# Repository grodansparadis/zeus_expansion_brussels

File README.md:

<h1>Zeus Expansion Brussels</h1>

Temperature add on card with Zeus expansion connector. Fits the 
<a href="http://www.grodansparadis.com/odessa/odessa.html">Odessa</a> module
among other modules.

<hr>

This project is part of the <a href="http://www.vscp.org">VSCP (Very Simple Control Protocol) project</a>. 

<hr>

This project is licensed under the 
<a href="http://creativecommons.org/licenses/by-nc-sa/3.0/">Creative Commons open source license Attribution-NonCommercial-ShareAlike 3.0 Unported</a>. 
Other license options are available by conacting <a href="malto:info@grodansparadis.com">Paradis of the Frog AB</a>

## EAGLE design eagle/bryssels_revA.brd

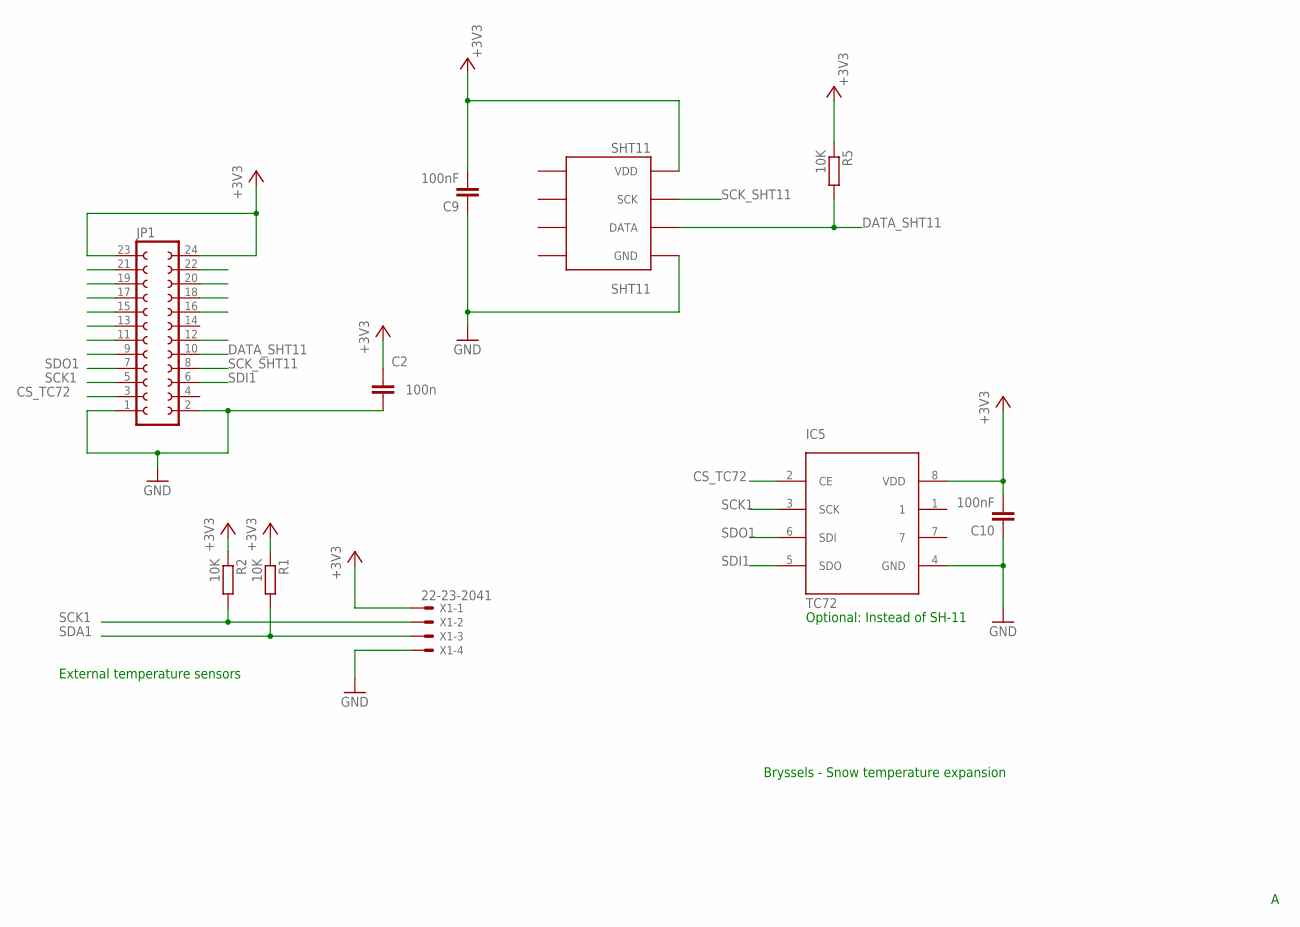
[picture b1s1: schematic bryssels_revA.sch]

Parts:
C2: 100n; C0805
C9, C10: 100nF; C0805
IC5: TC72; MSOP8
JP1: FE12-2
R1, R2, R5: 10K; M0805
SHT11: SHT11
X1: 22-23-2041

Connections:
+3V3: C2.1, C9.2, C10.2, IC5.8 (VDD), JP1.23, JP1.24, R1.1, R2.1, R5.1, SHT11.VDD, X1.1
CS_TC72: IC5.2 (CE), JP1.3
DATA_SHT11: JP1.10, R5.2, SHT11.DATA
GND: C2.2, C9.1, C10.1, IC5.4 (GND), JP1.1, JP1.2, SHT11.GND, X1.4
INT0: JP1.18
SCK1: IC5.3 (SCK), JP1.5, R2.2, X1.2
SCK_SHT11: JP1.8, SHT11.SCK
SDA1: R1.2, X1.3
SDI1: IC5.5 (SDO), JP1.6
SDO1: IC5.6 (SDI), JP1.7

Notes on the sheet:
Bryssels - Snow temperature expansion
Optional: Instead of SH-11
External temperature sensors

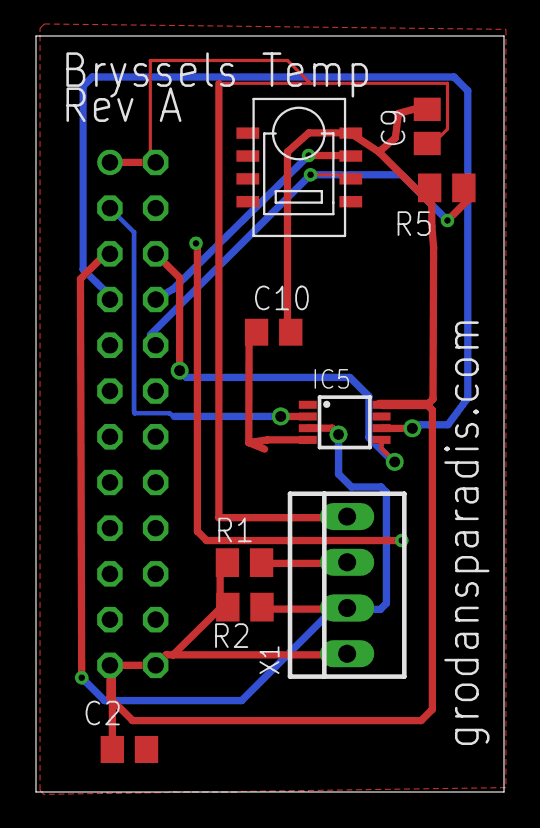
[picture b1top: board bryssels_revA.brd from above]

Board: 2 copper layers, 26.0 x 42.0 mm, 10 parts (1 on the bottom side), 9 nets.

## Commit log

2015-11-03 Make the design open
2015-11-03 Removed some junk
2015-11-03 Moved some design files from the root
2015-12-17 Updateded license and readme
